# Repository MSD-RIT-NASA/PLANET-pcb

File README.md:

<div id="top"></div>

<!-- PROJECT SHIELDS -->
<!--
*** I'm using markdown "reference style" links for readability.
*** Reference links are enclosed in brackets [ ] instead of parentheses ( ).
*** See the bottom of this document for the declaration of the reference variables
*** for contributors-url, forks-url, etc. This is an optional, concise syntax you may use.
*** https://www.markdownguide.org/basic-syntax/#reference-style-links
-->

<!-- PROJECT LOGO -->
<br />
<div align="center">

  <h3 align="center">PLANETS PCB</h3>

  <p align="center">
    The pcb for the connector board. This is to negate the excess use of wires and fit snuggly into the case.
  </p>
</div>

<!-- TABLE OF CONTENTS -->
<details>
  <summary>Table of Contents</summary>
  <ol>
    <li>
      <a href="#about-the-project">About The Project</a>
      <ul>
        <li><a href="#built-with">Built With</a></li>
      </ul>
    </li>
    <li><a href="#Component List">Component List</a></li>
    <li><a href="#block-diagram">Block Diagram</a></li>
    <li><a href="#schematic">Schematic</a></li>
    <li><a href="#pcb-layout">PCB Layout</a></li>
    <li><a href="#dimensions">Dimensions</a></li>
    <li><a href="#order details">Order Details</a></li>
    <li><a href="#contact">Contact</a></li>
  </ol>
</details>

<!-- ABOUT THE PROJECT -->
## About the Project

Project Link: [https://github.com/MSD-RIT-NASA](https://github.com/MSD-RIT-NASA)

This PCB was created for the intention to be used with the Gamification and Performanced Based Monitoring of Sensorimotor Activities project with NASA. This project, also known as PLANETs, is being developed by a Multidiciplinary Team at RIT. The objective of the project is to train an astronauts sense of blance when they return from long suspended time in space or to adapt themselves to a new planet's gravity. The game was meant to be a fun and competitive way to train the balance and activly collect and calculate data on their performace. These sensors interface with the SlimeVR program to create a skeleton that configures a persons center of balance, and creates a score. Another sensor is used under a balance board to relay the rotation of the board to the game. The game reflects a position back to the player in order to encourage them to adjust the angle of the balance board according to the game. The game awards the adjusted balance with game points, and negates points when they do not accuratly move the board. 

[![Front of PCB][front-3dview]]()
[![Back of PCB][back-3dview]]()

<p align="right">(<a href="#top">back to top</a>)</p>

### Built With

The pcb and schematic were designed in KiCad and ordered on JLCPCB

* [KiCad](https://www.kicad.org/)
* [JLCPCB](https://jlcpcb.com/)

<p align="right">(<a href="#top">back to top</a>)</p>

<!-- Component List -->
## Component List

Name | Symbol | Footprint | Purchase Link
--- | --- | --- | ---
RGB LED | Device:LED_RGBK | LED_THT:LED_D5.0mm-4_RGB | [LINK](https://www.sparkfun.com/products/9264)
150Ω | Device:R | 150Ω | [LINK](https://www.amazon.com/BOJACK-Values-Resistor-Resistors-Assortment/dp/B08FD1XVL6/ref=sr_1_3?crid=376HQO3UGCP0Y&keywords=variety+of+resistors&qid=1677360743&sprefix=variety+of+resistors%2Caps%2C124&sr=8-3)
180KΩ | Device:R | 180KΩ | [LINK](https://www.digikey.com/en/products/detail/te-connectivity-passive-product/ROX3SJ180K/2390251)
3.7V Lipo Battery| --- | --- | [LINK](https://www.digikey.com/en/products/detail/jauch-quartz/LP503759JU-PCM-2-WIRES-70MM/9560991)
Battery Connector | Connector:Conn_01x02_Female | JST_PH_S2B-PH-K_02x2.00mm_Angled | [LINK](https://www.digikey.com/en/products/detail/jst-sales-america-inc/S2B-PH-K-S-LF-SN/926626) [LINK](https://www.digikey.com/en/products/detail/jst-sales-america-inc/PHR-2/608607)
1N5817 Diode | SlimeVRMotherBoard-cache:Diode_1N5817 | Diode_THT:D_DO-41_SOD81_P10.16mm_Horizontal | [LINK](https://www.digikey.com/en/products/detail/stmicroelectronics/1N5817/770971)
1N5817 Diode | SlimeVRMotherBoard-cache:Diode_1N5817 | Diode_THT:D_DO-41_SOD81_P10.16mm_Horizontal | [LINK](https://www.digikey.com/en/products/detail/stmicroelectronics/1N5817/770971)
TP4056 Type-C | SlimeVRLibrary:4056Board | 4056Board | [LINK](https://www.amazon.com/gp/product/B07PZ6V937/ref=ppx_yo_dt_b_search_asin_title?ie=UTF8&psc=1)
Switch | SlimeVRLibrary:SlideSwitch | Wowoone_Slide_Switch_5mm | [LINK](https://www.amazon.com/gp/product/B07XSJYYYB/ref=ppx_yo_dt_b_search_asin_title?ie=UTF8&psc=1)
D1 mini | wemos_mini:WeMos_D1_mini | wemos-d1-mini-with-pin-header-and-connector | [LINK](https://www.amazon.com/gp/product/B081PX9YFV/ref=ppx_yo_dt_b_asin_title_o02_s00?ie=UTF8&th=1)
BNO085 Sensor | BNO085:4754 | BNO085 | [LINK](https://www.digikey.com/en/products/detail/adafruit-industries-llc/4754/13426653)
BNO085 AUX Sensor Connector | Connector:Conn_01x05_Female | JST_XH_S05B-XH-A_05x2.50mm_Angled | [LINK](https://www.digikey.com/en/products/detail/jst-sales-america-inc./S5B-XH-A-1(LF)(SN)/9961924) [LINK](https://www.digikey.com/en/products/detail/jst-sales-america-inc/XHP-5/1125486)
Status Rail Connector | Connector:Conn_01x05_Female | fivePinConn | ---

<p align="right">(<a href="#top">back to top</a>)</p>

<!-- BLOCK DIAGRAM -->
## Block Diagram
[![Block Diagram][block-diagram]]()

<!-- SCHEMATIC -->
## Schematic
[![schematic][schematic]]()

<!-- PCB LAYOUT -->
## PCB Layout
[![pcb-layout][pcb-layout]]()

<!-- DIMENSIONS -->
## Dimensions

PCB Dimensions: 71.394mm x 41.148mm

<!-- Order Details -->
## Order Details
[![order1][order1]]()
[![order2][order2]]()

Note: A non-green (in this case, black) PCB takes shipping 2 days longer

<!-- CONTACT -->
## Contact
Name | Major | email | github | year
--- | --- | --- | --- | ---
Angela Hudak | CE | ach2414@rit.edu | angelahudak | 2023
Corey Sheridan | CE | cjs5445@rit.edu | cjs5445 | 2023

<!-- MARKDOWN LINKS & IMAGES -->
<!-- https://www.markdownguide.org/basic-syntax/#reference-style-links -->

[block-diagram]: images/block_diagram.png
[schematic]: images/schematic.png
[front-3dview]: images/front_v1.PNG
[back-3dview]: images/back_v1.PNG
[order1]: images/order.PNG
[order2]: images/order2.PNG
[pcb-layout]: images/pcb-layout.PNG

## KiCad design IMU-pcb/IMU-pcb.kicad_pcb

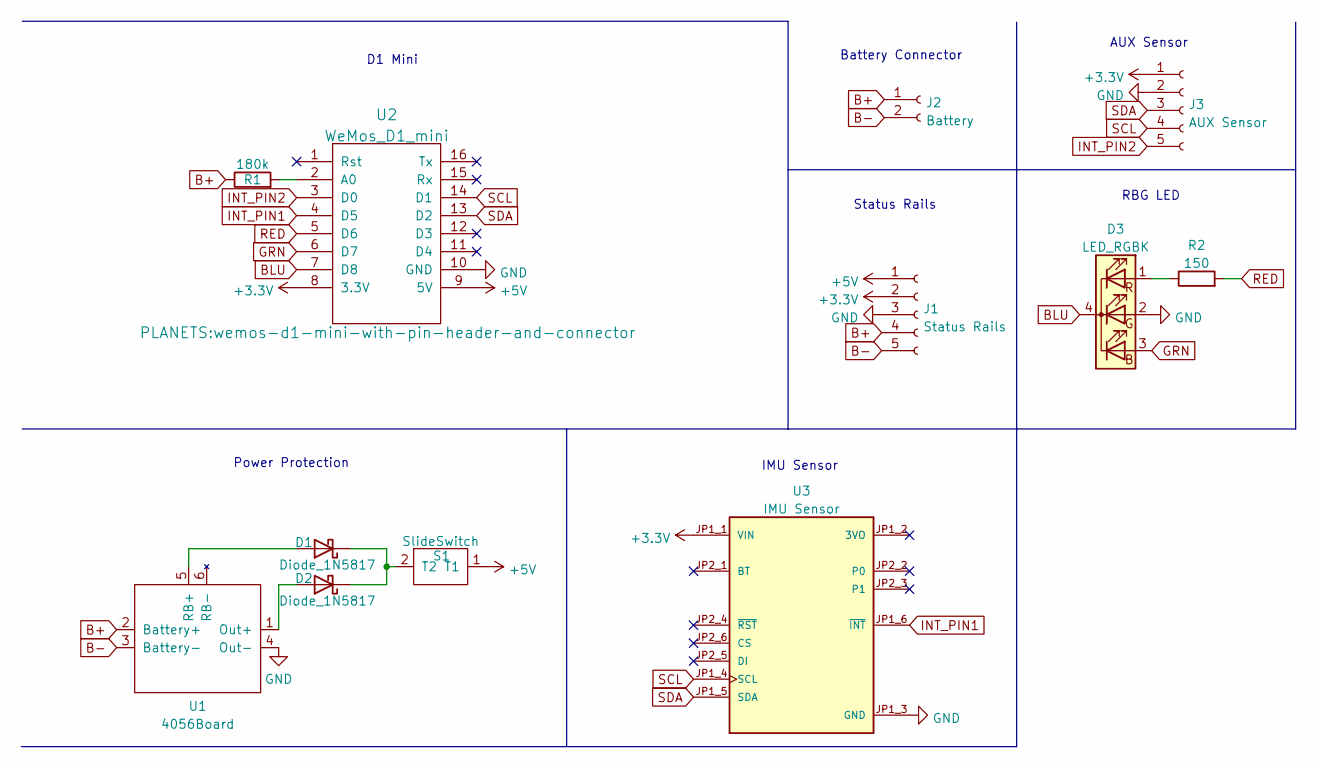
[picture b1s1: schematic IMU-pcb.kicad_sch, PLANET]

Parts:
D1, D2: Diode_1N5817; D_DO-41_SOD81_P10.16mm_Horizontal
D3: LED_RGBK; LED_D5.0mm-4_RGB
J1: Status Rails; fivePinConn
J2: Battery; JST_PH_S2B-PH-K_02x2.00mm_Angled
J3: AUX Sensor; JST_XH_S05B-XH-A_05x2.50mm_Angled
R1: 180k; 180KOhm
R2: 150; 150Ohm
S1: SlideSwitch; Wowoone_Slide_Switch_5mm
U1: 4056Board
U2: WeMos_D1_mini; wemos-d1-mini-with-pin-header-and-connector
U3: IMU Sensor; BNO085; PARTREV 2021-03-16

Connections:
+3.3V: J1.2, J3.1, U2.8 (3.3V), U3.JP1_1 (VIN)
+5V: J1.1, S1.1 (T1), U2.9 (5V)
B+: J1.4, J2.1, R1.1, U1.2 (Battery+)
B-: J1.5, J2.2, U1.3 (Battery-)
BLU: D3.4 (K), U2.7 (D8)
GND: D3.2 (GA), J1.3, J3.2, U1.4 (Out-), U2.10 (GND), U3.JP1_3 (GND)
GRN: D3.3 (BA), U2.6 (D7)
INT_PIN1: U2.4 (D5), U3.JP1_6 (~INT)
INT_PIN2: J3.5, U2.3 (D0)
unnamed: D1.1 (K), D2.1 (K), S1.2 (T2)
unnamed: D1.2 (A), U1.5 (RB+)
unnamed: D2.2 (A), U1.1 (Out+)
unnamed: D3.1 (RA), R2.1
unnamed: R1.2, U2.2 (A0)
RED: R2.2, U2.5 (D6)
SCL: J3.4, U2.14 (D1), U3.JP1_4 (SCL)
SDA: J3.3, U2.13 (D2), U3.JP1_5 (SDA)

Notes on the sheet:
RBG LED
Status Rails
IMU Sensor
Battery Connector
Power Protection
D1 Mini
AUX Sensor

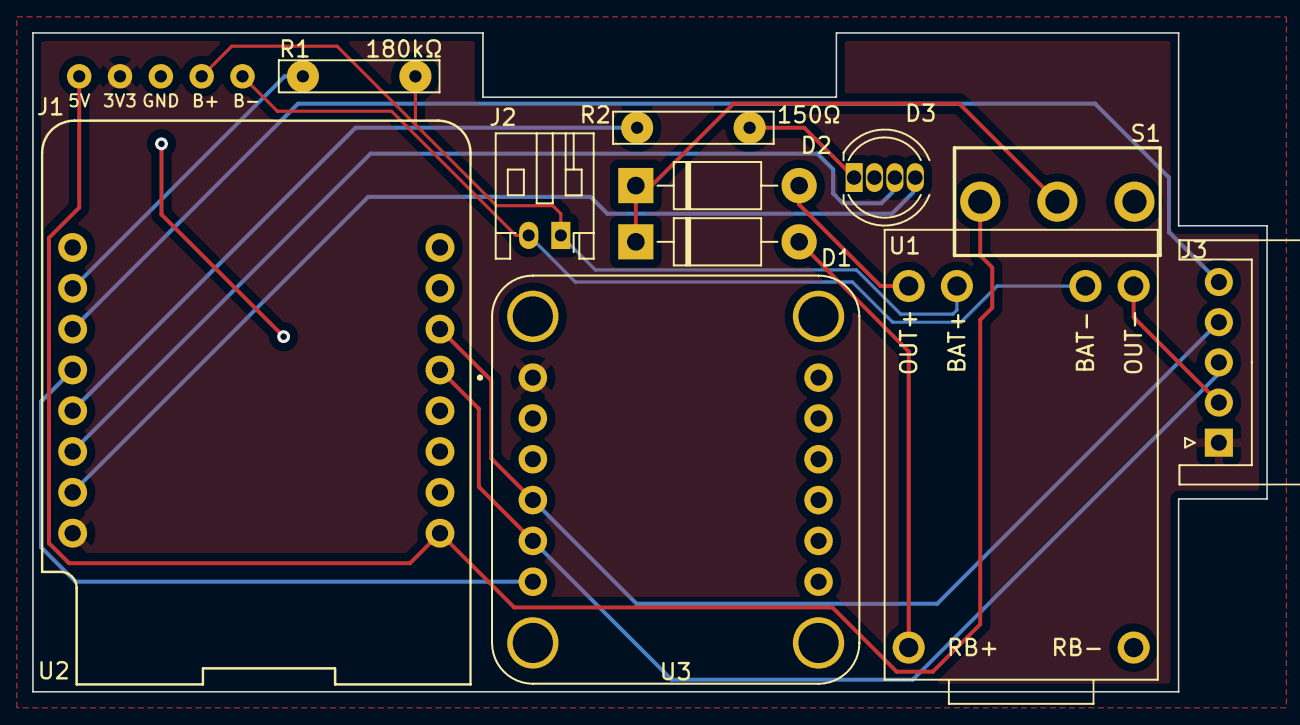
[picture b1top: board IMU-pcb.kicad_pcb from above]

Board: 2 copper layers, 76.8 x 41.0 mm, 12 parts (0 on the bottom side), 17 nets.

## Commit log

2023-02-02 Create test
2023-02-02 Schematic image
2023-02-02 Adding schematic to README
2023-02-08 Mesaurements and initial requirements
2023-02-08 completed Schematic and started PCB Layout
2023-02-13 formalized schematic, symbols, and footprints
2023-02-13 Test purchase link
2023-02-13 Purchase links
2023-02-14 Starting pcb layout
2023-02-14 fix logo
2023-02-14 Adjusting pcb layout to fit for the dimensions
2023-02-17 working on desktop
2023-02-17 Finished PCB layout and gerbers
2023-02-17 Adjusted README
2023-02-26 Finished v1.1 layout
2023-02-27 Adjusted pcb layout to be better
2023-03-31 adding 3D models for readme pic
2023-03-31 updated pictures
2023-03-31 adjusted 3d shapes
2023-04-01 about the project readme
2023-04-10 new version of PCB
2023-04-10 organzied gerbers
